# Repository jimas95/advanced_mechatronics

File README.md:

# advanced_mechatronics
433 Advanced Mechatronics Course

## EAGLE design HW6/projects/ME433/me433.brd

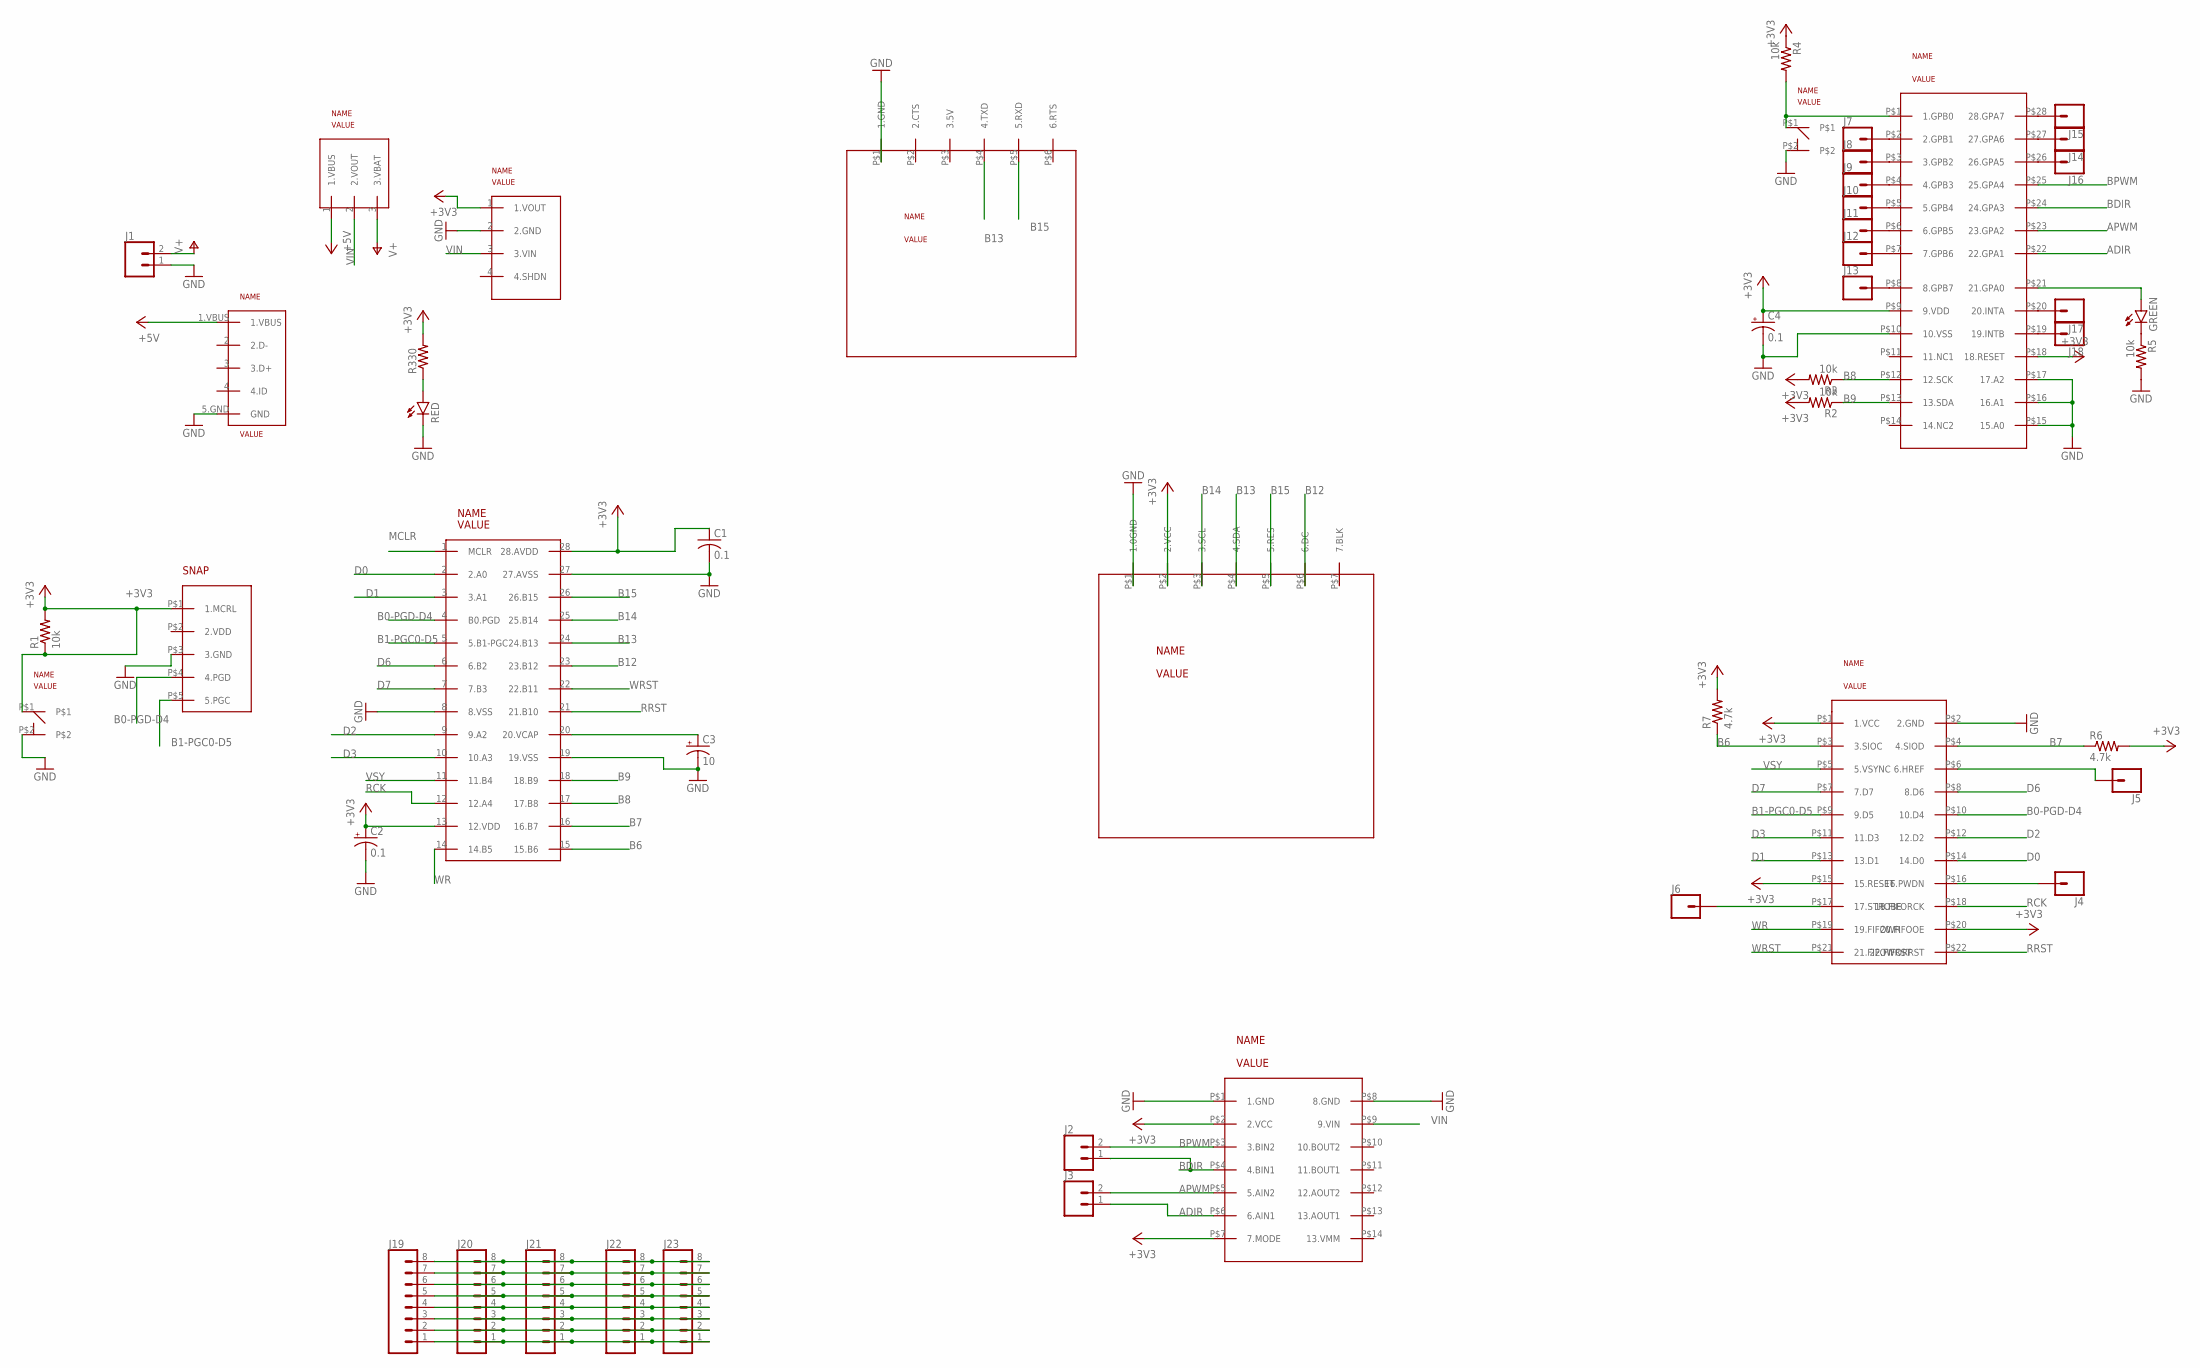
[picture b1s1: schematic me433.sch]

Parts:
C1: 0.1; C025-030X050
C2, C4: 0.1; B45181C
C3: 10; B45181C
GREEN: LED3MM
HBRIDGE: H_BRIDGE
J1, J2, J3: CONN_02; 1X02
J4, J5, J6, J7, J8, J9, J10, J11, J12, J13, J14, J15, J16, J17, J18: CONN_01; 1X01
J19, J20, J21, J22, J23: CONN_08"; 1X08
R1, R2, R3, R4, R5: 10k; 0207/10
R6, R7: 4.7k; 0207/10
R330: R-US_0207/10; 0207/10
RED: LED3MM
RESET: PUSH
U$1: PIC32; DIL28-3
U$2: MICROUSB
U$3: POLULU3V3; POLOLU3V3
U$4: SLIDE
U$5: FIFO_CAMERA
U$6: SNAP
U$7: USB_CON
U$8: LCD
U$10: EXPANDER
USER: PUSH

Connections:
+3V3: C1.1, C2.+, C4.+, HBRIDGE.P$2 (2.VCC), HBRIDGE.P$7 (7.MODE), R1.1, R1.2, R2.2, R3.2, R4.1, R6.2, R7.2, R330.2, RESET.P$1, U$1.13 (12.VDD), U$1.28 (28.AVDD), U$3.1 (1.VOUT), U$5.P$1 (1.VCC), U$5.P$15 (15.RESET), U$5.P$20 (20.FIFOOE), U$6.P$1 (1.MCRL), U$8.P$2 (2.VCC), U$10.P$9 (9.VDD), U$10.P$18 (18.RESET)
+5V: U$2.1.VBUS, U$4.1 (1.VBUS)
ADIR: HBRIDGE.P$6 (6.AIN1), J3.1, U$10.P$22 (22.GPA1)
APWM: HBRIDGE.P$5 (5.AIN2), J3.2, U$10.P$23 (23.GPA2)
B0-PGD-D4: U$1.4 (B0.PGD), U$5.P$10 (10.D4), U$6.P$4 (4.PGD)
B1-PGC0-D5: U$1.5 (5.B1-PGC), U$5.P$9 (9.D5), U$6.P$5 (5.PGC)
B6: R7.1, U$1.15 (15.B6), U$5.P$3 (3.SIOC)
B7: R6.1, U$1.16 (16.B7), U$5.P$4 (4.SIOD)
B8: R3.1, U$1.17 (17.B8), U$10.P$12 (12.SCK)
B9: R2.1, U$1.18 (18.B9), U$10.P$13 (13.SDA)
B12: U$1.23 (23.B12), U$8.P$6 (6.DC)
B13: U$1.24 (24.B13), U$7.P$4 (4.TXD), U$8.P$4 (4.SDA)
B14: U$1.25 (25.B14), U$8.P$3 (3.SCL)
B15: U$1.26 (26.B15), U$7.P$5 (5.RXD), U$8.P$5 (5.RES)
BDIR: HBRIDGE.P$4 (4.BIN1), J2.1, U$10.P$24 (24.GPA3)
BPWM: HBRIDGE.P$3 (3.BIN2), J2.2, U$10.P$25 (25.GPA4)
D0: U$1.2 (2.A0), U$5.P$14 (14.D0)
D1: U$1.3 (3.A1), U$5.P$13 (13.D1)
D2: U$1.9 (9.A2), U$5.P$12 (12.D2)
D3: U$1.10 (10.A3), U$5.P$11 (11.D3)
D6: U$1.6 (6.B2), U$5.P$8 (8.D6)
D7: U$1.7 (7.B3), U$5.P$7 (7.D7)
GND: C1.2, C2.-, C3.-, C4.-, HBRIDGE.P$1 (1.GND), HBRIDGE.P$8 (8.GND), J1.1, R5.2, RED.K (C), RESET.P$2, U$1.8 (8.VSS), U$1.19 (19.VSS), U$1.27 (27.AVSS), U$2.5.GND (GND), U$3.2 (2.GND), U$5.P$2 (2.GND), U$6.P$3 (3.GND), U$7.P$1 (1.GND), U$8.P$1 (1.0GND), U$10.P$10 (10.VSS), U$10.P$15 (15.A0), U$10.P$16 (16.A1), U$10.P$17 (17.A2), USER.P$2
MCLR: U$1.1 (MCLR)
unnamed: C3.+, U$1.20 (20.VCAP)
unnamed: R330.1, RED.A
unnamed: GREEN.A, U$10.P$21 (21.GPA0)
unnamed: R4.2, U$10.P$1 (1.GPB0), USER.P$1
unnamed: GREEN.K (C), R5.1
unnamed: J6.1, U$5.P$17 (17.STROBE)
unnamed: J4.1, U$5.P$16 (16.PWDN)
unnamed: J5.1, U$5.P$6 (6.HREF)
unnamed: J7.1, U$10.P$2 (2.GPB1)
unnamed: J8.1, U$10.P$3 (3.GPB2)
unnamed: J9.1, U$10.P$4 (4.GPB3)
unnamed: J10.1, U$10.P$5 (5.GPB4)
unnamed: J11.1, U$10.P$6 (6.GPB5)
unnamed: J12.1, U$10.P$7 (7.GPB6)
unnamed: J13.1, U$10.P$8 (8.GPB7)
unnamed: J14.1, U$10.P$27 (27.GPA6)
unnamed: J15.1, U$10.P$28 (28.GPA7)
unnamed: J16.1, U$10.P$26 (26.GPA5)
unnamed: J17.1, U$10.P$20 (20.INTA)
unnamed: J18.1, U$10.P$19 (19.INTB)
unnamed: J19.8, J20.8, J21.8, J22.8, J23.8
unnamed: J19.7, J20.7, J21.7, J22.7, J23.7
unnamed: J19.6, J20.6, J21.6, J22.6, J23.6
unnamed: J19.5, J20.5, J21.5, J22.5, J23.5
unnamed: J19.4, J20.4, J21.4, J22.4, J23.4
unnamed: J19.3, J20.3, J21.3, J22.3, J23.3
unnamed: J19.2, J20.2, J21.2, J22.2, J23.2
unnamed: J19.1, J20.1, J21.1, J22.1, J23.1
RCK: U$1.12 (12.A4), U$5.P$18 (18.FIFORCK)
RRST: U$1.21 (21.B10), U$5.P$22 (22.FIFORRST)
V+: J1.2, U$4.3 (3.VBAT)
VIN: HBRIDGE.P$9 (9.VIN), U$3.3 (3.VIN), U$4.2 (2.VOUT)
VSY: U$1.11 (11.B4), U$5.P$5 (5.VSYNC)
WR: U$1.14 (14.B5), U$5.P$19 (19.FIFOWR)
WRST: U$1.22 (22.B11), U$5.P$21 (21.FIFOWRST)

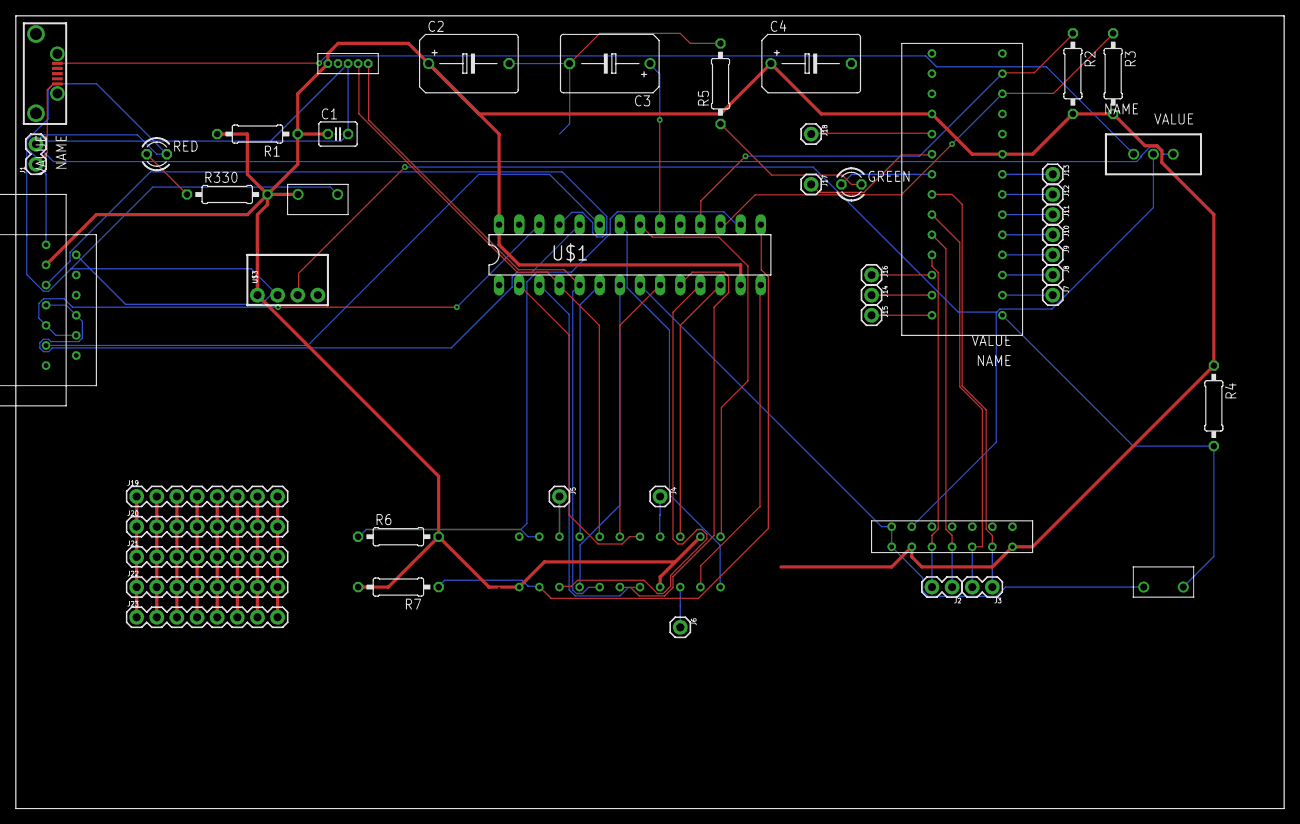
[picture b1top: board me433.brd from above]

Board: 2 copper layers, 160.0 x 100.0 mm, 49 parts (0 on the bottom side), 58 nets.

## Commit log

2021-04-06 added sample files
2021-04-06 ignoring python chace file
2021-04-06 working on it
2021-04-06 added fft functions and subplot
2021-04-07 final code and plots of Q2
2021-04-07 rename file, add Q6 data
2021-04-07 working on Q7
2021-04-07 remove commencts, added printing more info
2021-04-08 fix fft bug
2021-04-08 upload new plots
2021-04-08 new plot fod D signal
2021-04-08 added plots of Q7
2021-04-08 added code for Q7
2021-04-08 filter gains for Q7
2021-04-08 final code
2021-04-17 upload image of kit
2021-04-27 added images of homework
2021-04-27 code added
2021-05-06 code for homwork 5
2021-05-18 added hw 6
2021-05-18 added images
2021-05-24 added homework 7
2021-05-26 upload code for HW8
2021-05-26 fix bug
2021-05-30 init files
2021-05-30 added main fail
2021-05-30 added questionmark char
2021-05-30 added my functions
2021-05-30 added control bits
2021-05-30 working drawing strings
2021-05-30 working writing strings on LCD
2021-05-30 added image result
2021-05-30 added final code, working show fps and bar display
2021-06-06 upload HW10
2021-06-10 added bracket for motor mount
2021-06-10 added code for HW11
